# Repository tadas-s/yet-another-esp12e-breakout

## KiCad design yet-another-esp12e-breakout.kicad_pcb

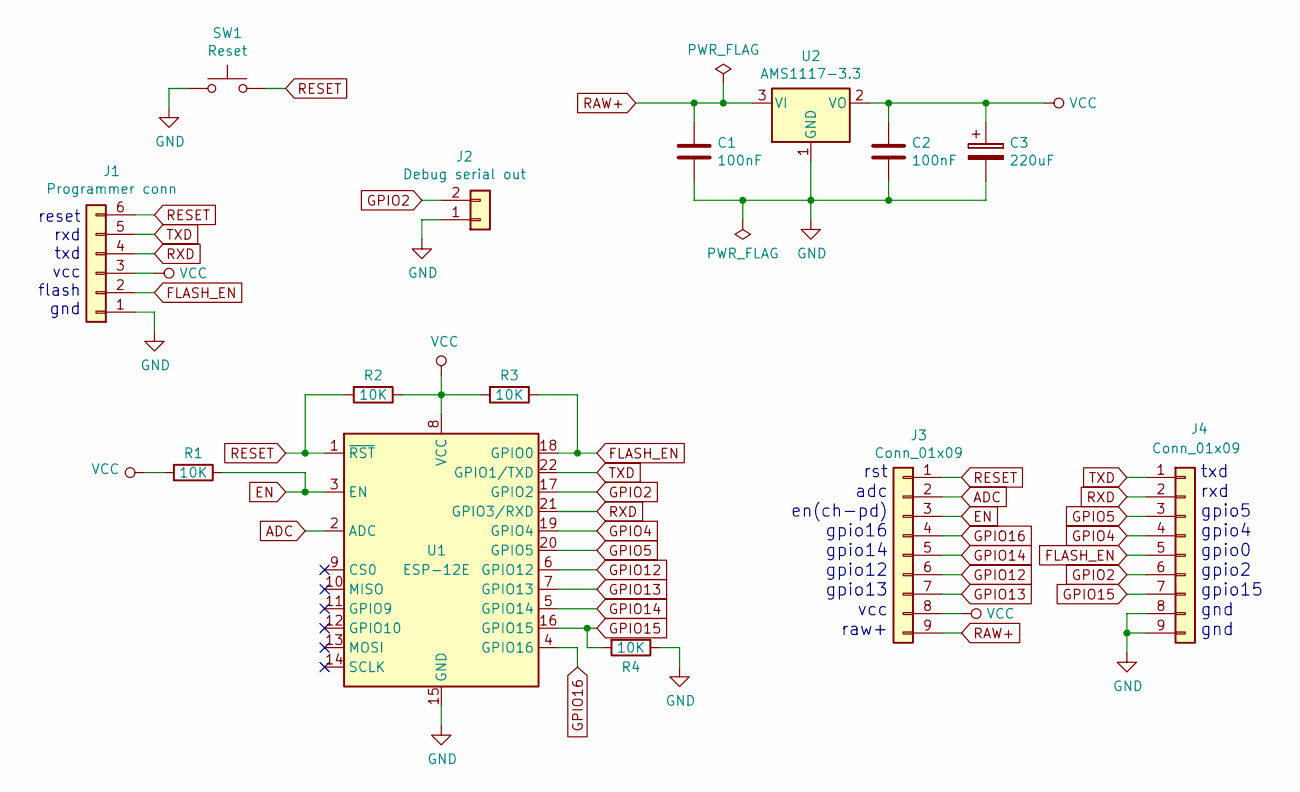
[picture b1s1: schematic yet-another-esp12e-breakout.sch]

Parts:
C1, C2: 100nF; C_0805_2012Metric_Pad1.15x1.40mm_HandSolder
C3: 220uF; CP_Elec_6.3x5.8
J1: Programmer conn; PinHeader_1x06_P2.54mm_Vertical
J2: Debug serial out; PinHeader_1x02_P2.54mm_Vertical
J3, J4: Conn_01x09; PinHeader_1x09_P2.54mm_Vertical
R1, R2, R3, R4: 10K; R_0805_2012Metric_Pad1.15x1.40mm_HandSolder
SW1: Reset; SW_SPST_B3S-1000
U1: ESP-12E
U2: AMS1117-3.3; SOT-223-3_TabPin2

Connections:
ADC: J3.2, U1.2 (ADC)
EN: J3.3, R1.1, U1.3 (EN)
FLASH_EN: J1.2, J4.5, R3.1, U1.18 (GPIO0)
GND: C1.2, C2.2, C3.2, J1.1, J2.1, J4.8, J4.9, R4.1, SW1.1, U1.15 (GND), U2.1 (GND)
GPIO2: J2.2, J4.6, U1.17 (GPIO2)
GPIO4: J4.4, U1.19 (GPIO4)
GPIO5: J4.3, U1.20 (GPIO5)
GPIO12: J3.6, U1.6 (GPIO12)
GPIO13: J3.7, U1.7 (GPIO13)
GPIO14: J3.5, U1.5 (GPIO14)
GPIO15: J4.7, R4.2, U1.16 (GPIO15)
GPIO16: J3.4, U1.4 (GPIO16)
RAW+: C1.1, J3.9, U2.3 (VI)
RESET: J1.6, J3.1, R2.2, SW1.2, U1.1 (~RST)
RXD: J1.4, J4.2, U1.21 (GPIO3/RXD)
TXD: J1.5, J4.1, U1.22 (GPIO1/TXD)
VCC: C2.1, C3.1, J1.3, J3.8, R1.2, R2.1, R3.2, U1.8 (VCC), U2.2 (VO)

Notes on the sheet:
reset rxd txd vcc flash gnd
rst adc en(ch-pd) gpio16 gpio14 gpio12 gpio13 vcc raw+
txd rxd gpio5 gpio4 gpio0 gpio2 gpio15 gnd gnd

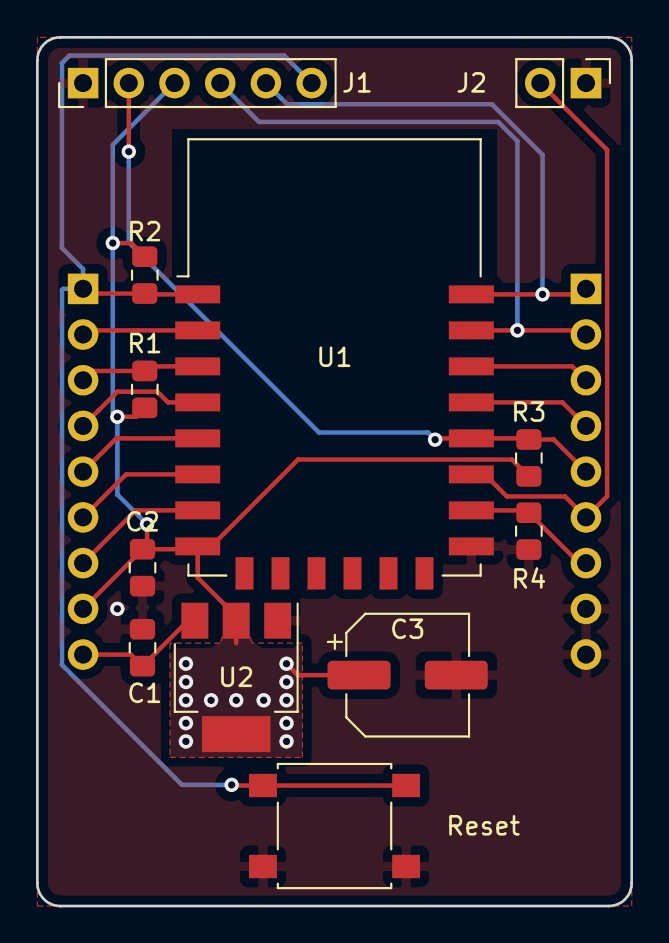
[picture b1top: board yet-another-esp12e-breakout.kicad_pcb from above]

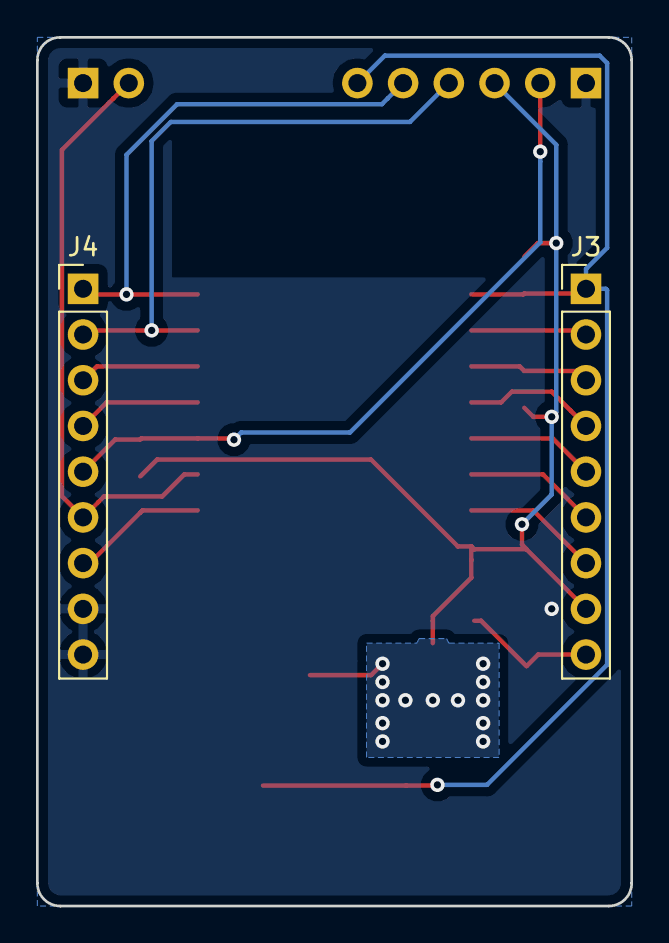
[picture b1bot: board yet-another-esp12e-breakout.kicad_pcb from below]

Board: 2 copper layers, 33.0 x 48.3 mm, 14 parts (2 on the bottom side), 17 nets.

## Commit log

2019-02-24 Blank KiCad project
2019-02-24 Initial (untested) schematic + PCB.
    Yet another ESP-12E/F breakout board for breadboards.
    Features:
    * Programming header with reset/flash en lines
    * Debug seriau out (via uart1)
    * Always boots in custom firmware mode (not for "at modem" use).
    * Reset button.
2019-02-24 Misc: cleanup from .bak files
